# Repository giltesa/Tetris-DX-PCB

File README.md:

# Tetris DX for Game Boy: Custom Motherboard

This is a full-color printed custom motherboard for the game Tetris DX for Game Boy. You can use it to customize your original Tetris DX, which may have lost its battery since it was released in 1998 and may have a damaged/rusted circuit. Additionally, as you can see in the photos, this new circuit will give an incredible look to your Tetris DX. Remember to use a transparent Game Boy or Game Boy Color shell to display it in all its splendor.

Full color Silkscreen:

Custom Motherboard, not assambled yet:

PCB in standard green color, just for testing the circuit:

"Original PCB circuit used as a donor for the game:

## Would you like it?

[**Tetris DX for Game Boy: Custom Motherboard**](https://shop.giltesa.com/?p=2066)

## License

This project is licensed under a **Creative Commons** license:
**[Attribution-NonCommercial-ShareAlike 4.0 International (CC BY-NC-SA 4.0) ](https://creativecommons.org/licenses/by-nc-sa/4.0/)**

Check the [LICENSE.md](LICENSE.md) for more information.

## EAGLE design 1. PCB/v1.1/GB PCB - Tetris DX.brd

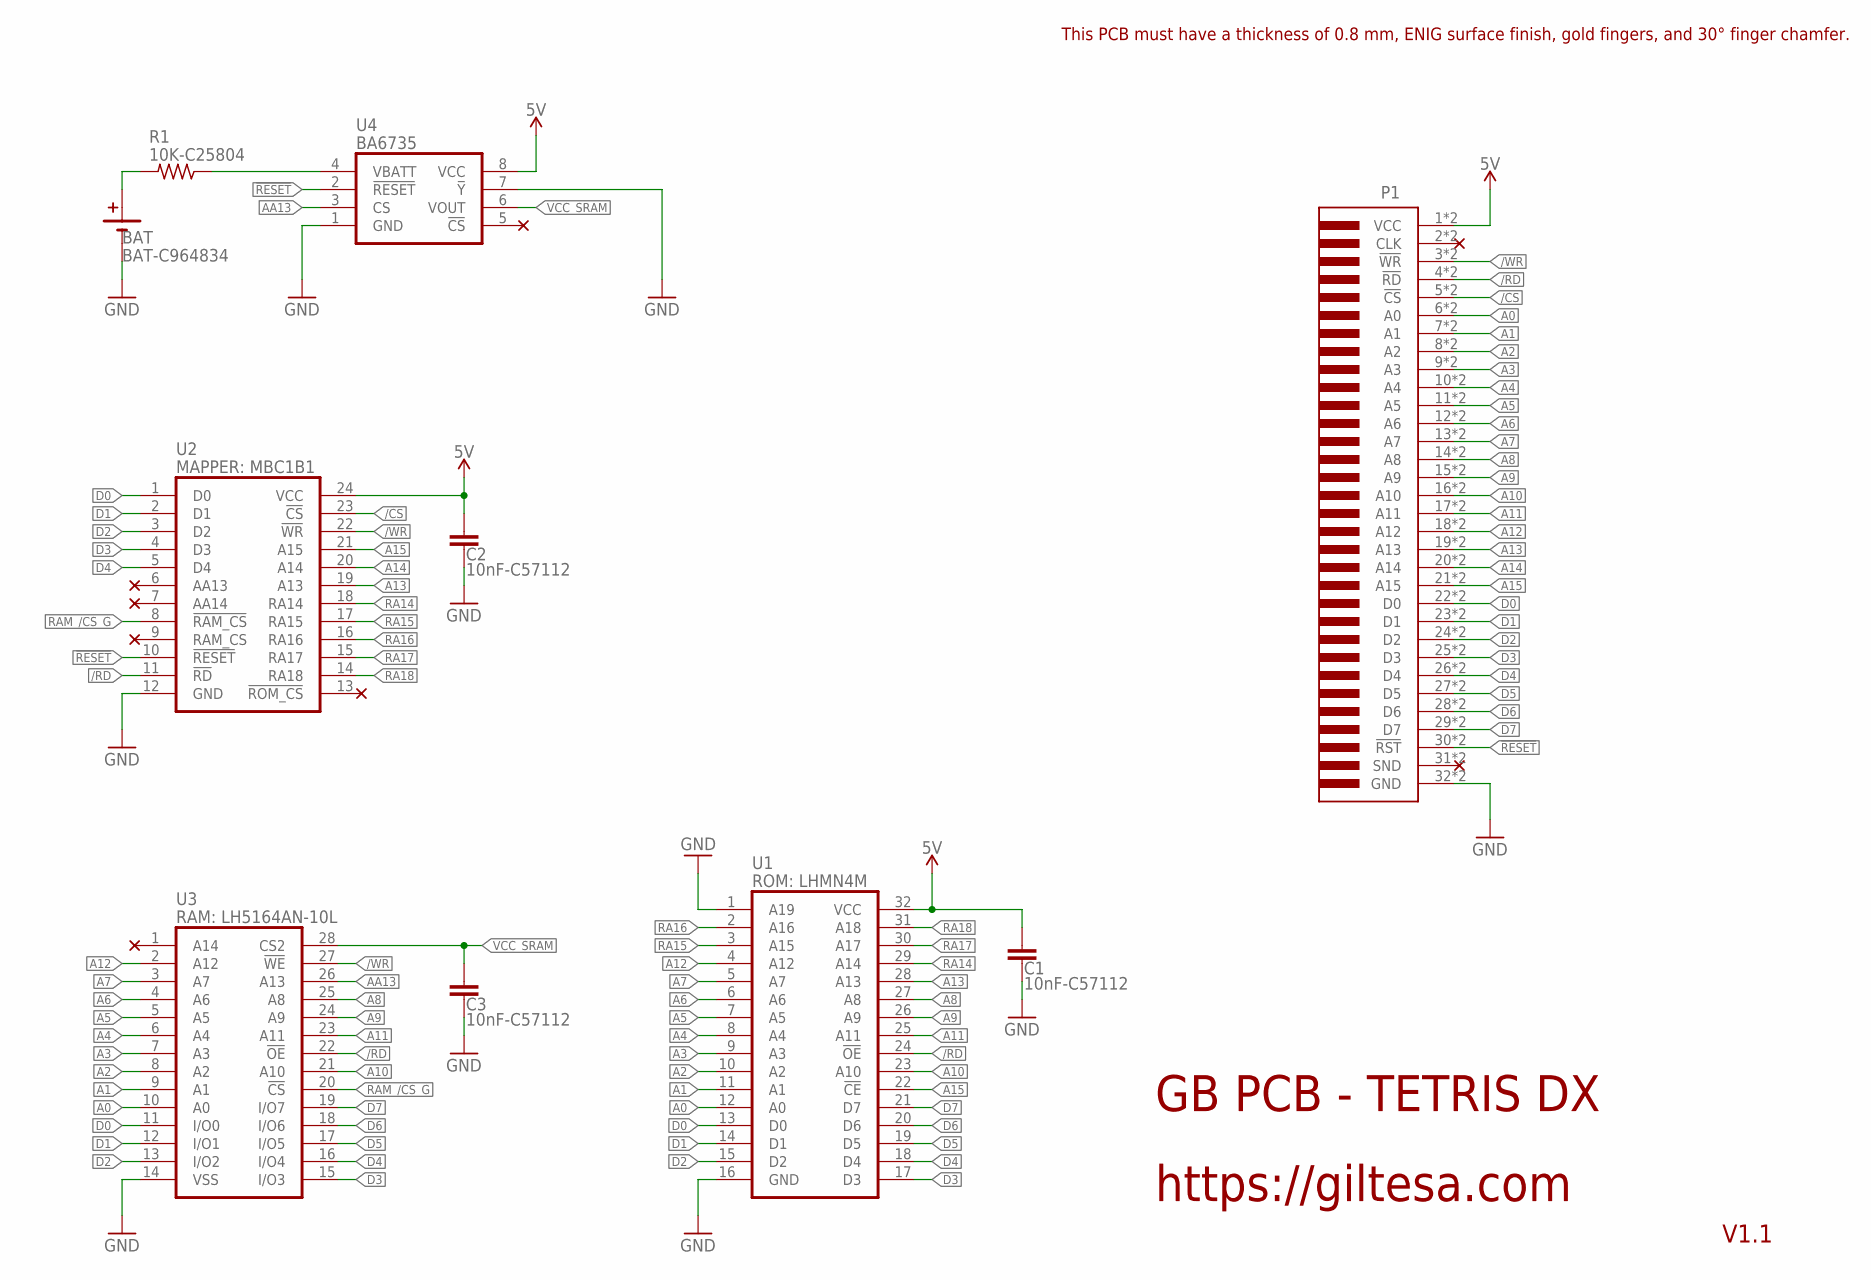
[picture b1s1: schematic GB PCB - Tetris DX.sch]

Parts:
BAT: BAT-C964834; CR2032_MY-2032-12-R
C1, C2, C3: 10nF-C57112; C0603
P1: GB_CARTRIDGE
R1: 10K-C25804; R0603
U1: ROM: LHMN4M; LHMN4M
U2: MAPPER: MBC1B1; MBC1B1
U3: RAM: LH5164AN-10L; LH5164AN-10L
U4: BA6735

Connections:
5V: C1.2, C2.1, P1.1 (VCC), P1.1" (VCC), U1.32 (VCC), U2.24 (VCC), U4.8 (VCC)
!RESET: P1.30 (!RST), P1.30" (!RST), U2.10 (!RESET), U4.2 (!RESET)
/CS: P1.5 (!CS), P1.5" (!CS), U2.23 (!CS)
/RD: P1.4 (!RD), P1.4" (!RD), U1.24 (!OE), U2.11 (!RD), U3.22 (!OE)
/WR: P1.3 (!WR), P1.3" (!WR), U2.22 (!WR), U3.27 (!WE)
A0: P1.6 (A0), P1.6" (A0), U1.12 (A0), U3.10 (A0)
A1: P1.7 (A1), P1.7" (A1), U1.11 (A1), U3.9 (A1)
A2: P1.8 (A2), P1.8" (A2), U1.10 (A2), U3.8 (A2)
A3: P1.9 (A3), P1.9" (A3), U1.9 (A3), U3.7 (A3)
A4: P1.10 (A4), P1.10" (A4), U1.8 (A4), U3.6 (A4)
A5: P1.11 (A5), P1.11" (A5), U1.7 (A5), U3.5 (A5)
A6: P1.12 (A6), P1.12" (A6), U1.6 (A6), U3.4 (A6)
A7: P1.13 (A7), P1.13" (A7), U1.5 (A7), U3.3 (A7)
A8: P1.14 (A8), P1.14" (A8), U1.27 (A8), U3.25 (A8)
A9: P1.15 (A9), P1.15" (A9), U1.26 (A9), U3.24 (A9)
A10: P1.16 (A10), P1.16" (A10), U1.23 (A10), U3.21 (A10)
A11: P1.17 (A11), P1.17" (A11), U1.25 (A11), U3.23 (A11)
A12: P1.18 (A12), P1.18" (A12), U1.4 (A12), U3.2 (A12)
A13: P1.19 (A13), P1.19" (A13), U1.28 (A13), U2.19 (A13)
A14: P1.20 (A14), P1.20" (A14), U2.20 (A14)
A15: P1.21 (A15), P1.21" (A15), U1.22 (!CE), U2.21 (A15)
AA13: U3.26 (A13), U4.3 (CS)
D0: P1.22 (D0), P1.22" (D0), U1.13 (D0), U2.1 (D0), U3.11 (I/O0)
D1: P1.23 (D1), P1.23" (D1), U1.14 (D1), U2.2 (D1), U3.12 (I/O1)
D2: P1.24 (D2), P1.24" (D2), U1.15 (D2), U2.3 (D2), U3.13 (I/O2)
D3: P1.25 (D3), P1.25" (D3), U1.17 (D3), U2.4 (D3), U3.15 (I/O3)
D4: P1.26 (D4), P1.26" (D4), U1.18 (D4), U2.5 (D4), U3.16 (I/O4)
D5: P1.27 (D5), P1.27" (D5), U1.19 (D5), U3.17 (I/O5)
D6: P1.28 (D6), P1.28" (D6), U1.20 (D6), U3.18 (I/O6)
D7: P1.29 (D7), P1.29" (D7), U1.21 (D7), U3.19 (I/O7)
GND: BAT.GND1 (B-), BAT.GND2 (B-), BAT.GND3 (B-), C1.1, C2.2, C3.2, P1.32 (GND), P1.32" (GND), U1.1 (A19), U1.16 (GND), U2.12 (GND), U3.14 (VSS), U4.1 (GND), U4.7 (!Y)
unnamed: BAT.VCC1 (B+), BAT.VCC2 (B+), R1.2
unnamed: R1.1, U4.4 (VBATT)
RA14: U1.29 (A14), U2.18 (RA14)
RA15: U1.3 (A15), U2.17 (RA15)
RA16: U1.2 (A16), U2.16 (RA16)
RA17: U1.30 (A17), U2.15 (RA17)
RA18: U1.31 (A18), U2.14 (RA18)
RAM_/CS_G: U2.8 (!RAM_CS), U3.20 (!CS)
VCC_SRAM: C3.1, U3.28 (CS2), U4.6 (VOUT)

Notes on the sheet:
GB PCB - TETRIS DX
https://giltesa.com
V1.1
This PCB must have a thickness of 0.8 mm, ENIG surface finish, gold fingers, and 30° finger chamfer.

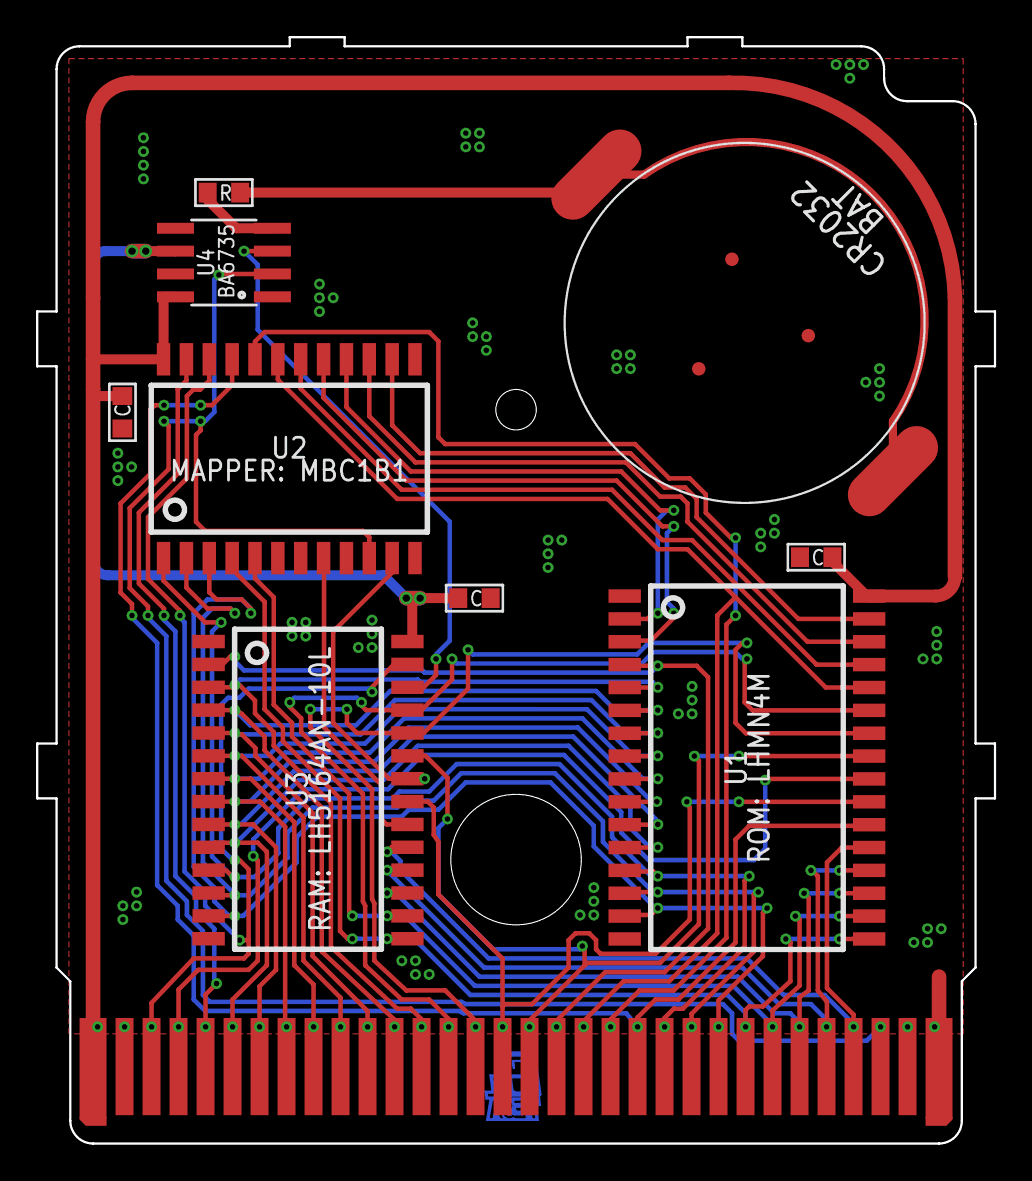
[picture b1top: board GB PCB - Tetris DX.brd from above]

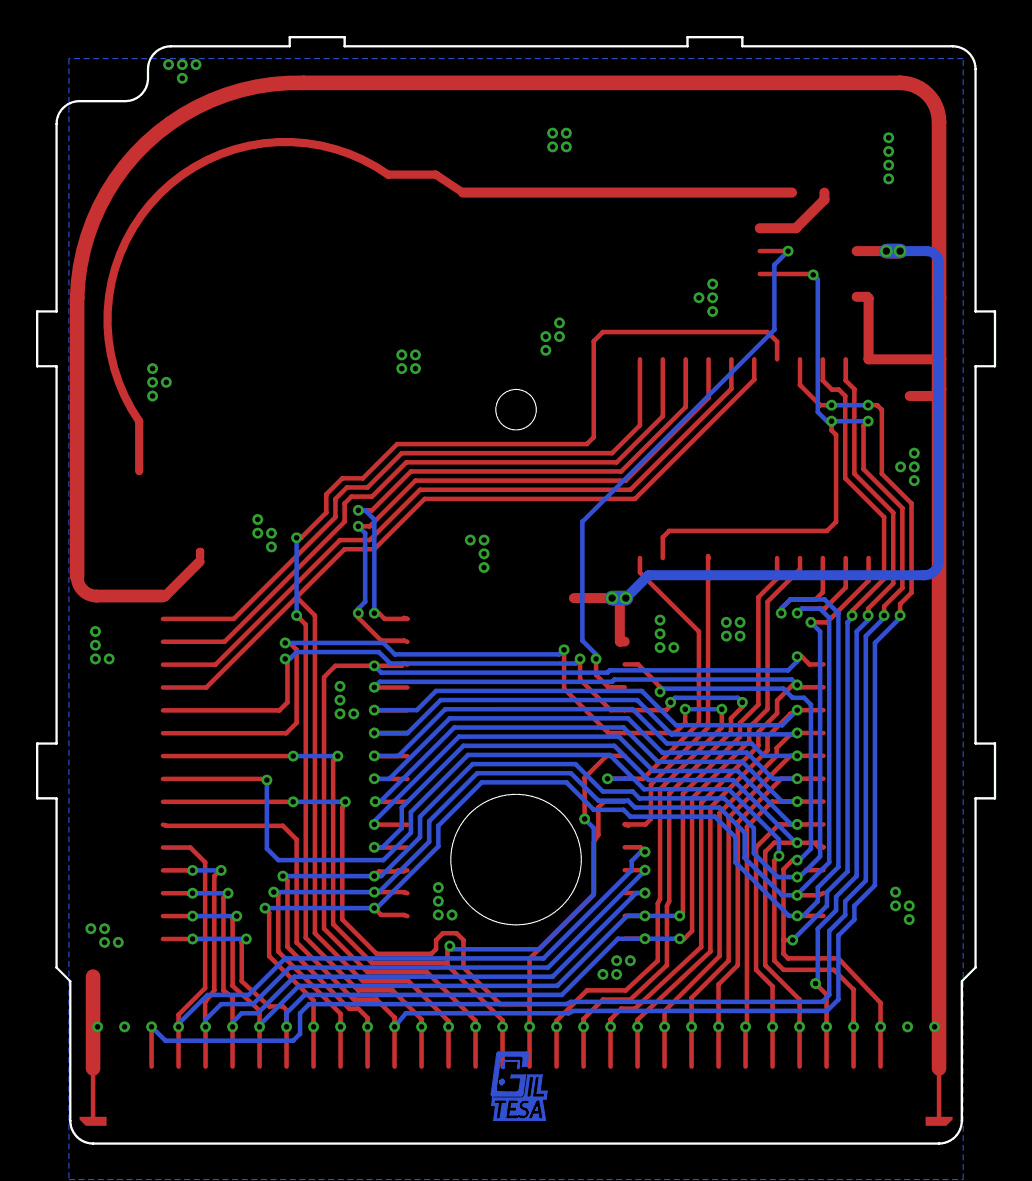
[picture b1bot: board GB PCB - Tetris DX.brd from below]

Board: 2 copper layers, 53.2 x 61.5 mm, 12 parts (2 on the bottom side), 40 nets.

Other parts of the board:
U$12: GILTESA_LOGO_COPPER
U$13: GILTESA.COM_7MM_STOP

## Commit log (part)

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2024-05-05 no message
2024-10-10 v1.0
2024-10-10 v1.1

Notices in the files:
parts and their libraries:
SparkFun: Licensing: CC v3.0 Share-Alike You are welcome to use this library for commercial purposes.
SparkFun-PowerSymbols: Licensing: Creative Commons ShareAlike 4.0 International - https://creativecommons.org/licenses/by-sa/4.0
